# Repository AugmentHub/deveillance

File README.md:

# Deveillance Devices
We started this project as we have seen an increase in potentially privacy invading devices, such as wearable AI necklace, AR glasses that can take pictures of you, and more. Throughout the 2024 Augmentation Residency, we - Aida Baradari, Treyden Chiaravalloti, and Nasibe Nur Dundar - were thinking about ways of building what we coin "deveillance" technologies. 

**Deveillance** means off-watching, and we define deveillance technologies as technologies that give the power to the individual as to what data is collected and what is not collected. This can take the form of digital data and data potentially collected in the real world. This is, fundamentally, to build the use of these technologies for good and protective measures rather than for malicious intentions. 

There is still a lot of work to be done and we need more engineers tackling the problems of data collection in all realms. We started with Audio but this is a hub for everyone to contribute to a better design of deveillance devices. 

## Audio
Audio Jammers have existed for a while now but has been increasingly difficult to find affordable ones or even good, structured tutorials of how to make your own. This is how we built an audio jammer and how this works.

We are using a motor driver - more specifically the H-Bridge - L298N in order to generate a square wave signal. We formally tried using a signal generator with an amplifier but found it more difficult to get a non-noisy signal. 
The generated square-wave signal is based on the input voltage, for which you can use a power supply for now but we will eventually add batteries that are high enough (to get a good power output, we are currently using the H-Bridge that go up to 30V and 2A) but when we make it more wearable and you want to use it on your shelf, you may want to use a DC-DC Converter, upping the voltage of a generic LiPo battery. 

We are explaining how the Physics behind this works and then also how to make it yourself. 

### Wait, but why does it work? 
In a very simple way of explaining, without needing much physics background: Microphones have diaphragms. When sound hits that diaphragm, it vibrates it, and that movement creates electrical signals (in an abstract way of explaining it). 
Now, sound has different frequencies. We can hear a certain range of frequencies (20Hz to 20kHz) but below or higher than that humans can generally not hear. If you are close enough to our hearing frequency, however, the diaphragm of the microphone can sometimes pick it up. 
And because of this, your voice will be overridden. It cannot be filtered out. 

### Make It Yourself
- [Transducers](https://en.wikipedia.org/wiki/Transducer): For the bigger version, we are currently using the [2223-CUSA-T601-150-2400-TH-ND](https://www.digikey.com/en/products/detail/same-sky-formerly-cui-devices/CUSA-T601-150-2400-TH/16579211). 
- Arduino Nano (or any other Arduino / microcontroller device)

**Putting Things Together**
Here is how we are currently wiring things together (though the topology is very likely to change) :

### PCB Design 
Within this directory you will also find a PCB design with the L298N chip on board, battery charging circuit and more included. 
The data parts we are using are the following: 

- TP4056: 1A Standalone Linear Li-Ion Battery Charger with Thermal Regulation. This is for charging our battery and is connected to a USB port. You can find the datasheet [here](https://dlnmh9ip6v2uc.cloudfront.net/datasheets/Prototyping/TP4056.pdf). 
- DW01A: this is a battery protection IC. You can read more about it [here](https://hmsemi.com/downfile/dw01a.pdf)
- XL6009: this is our boost converter IC, which has a wide bandwidth. Find more information [here](https://www.haoyuelectronics.com/Attachment/XL6009/XL6009-DC-DC-Converter-Datasheet.pdf).
- L298N: this is our Hbridge to create our Ultrasonic wave.

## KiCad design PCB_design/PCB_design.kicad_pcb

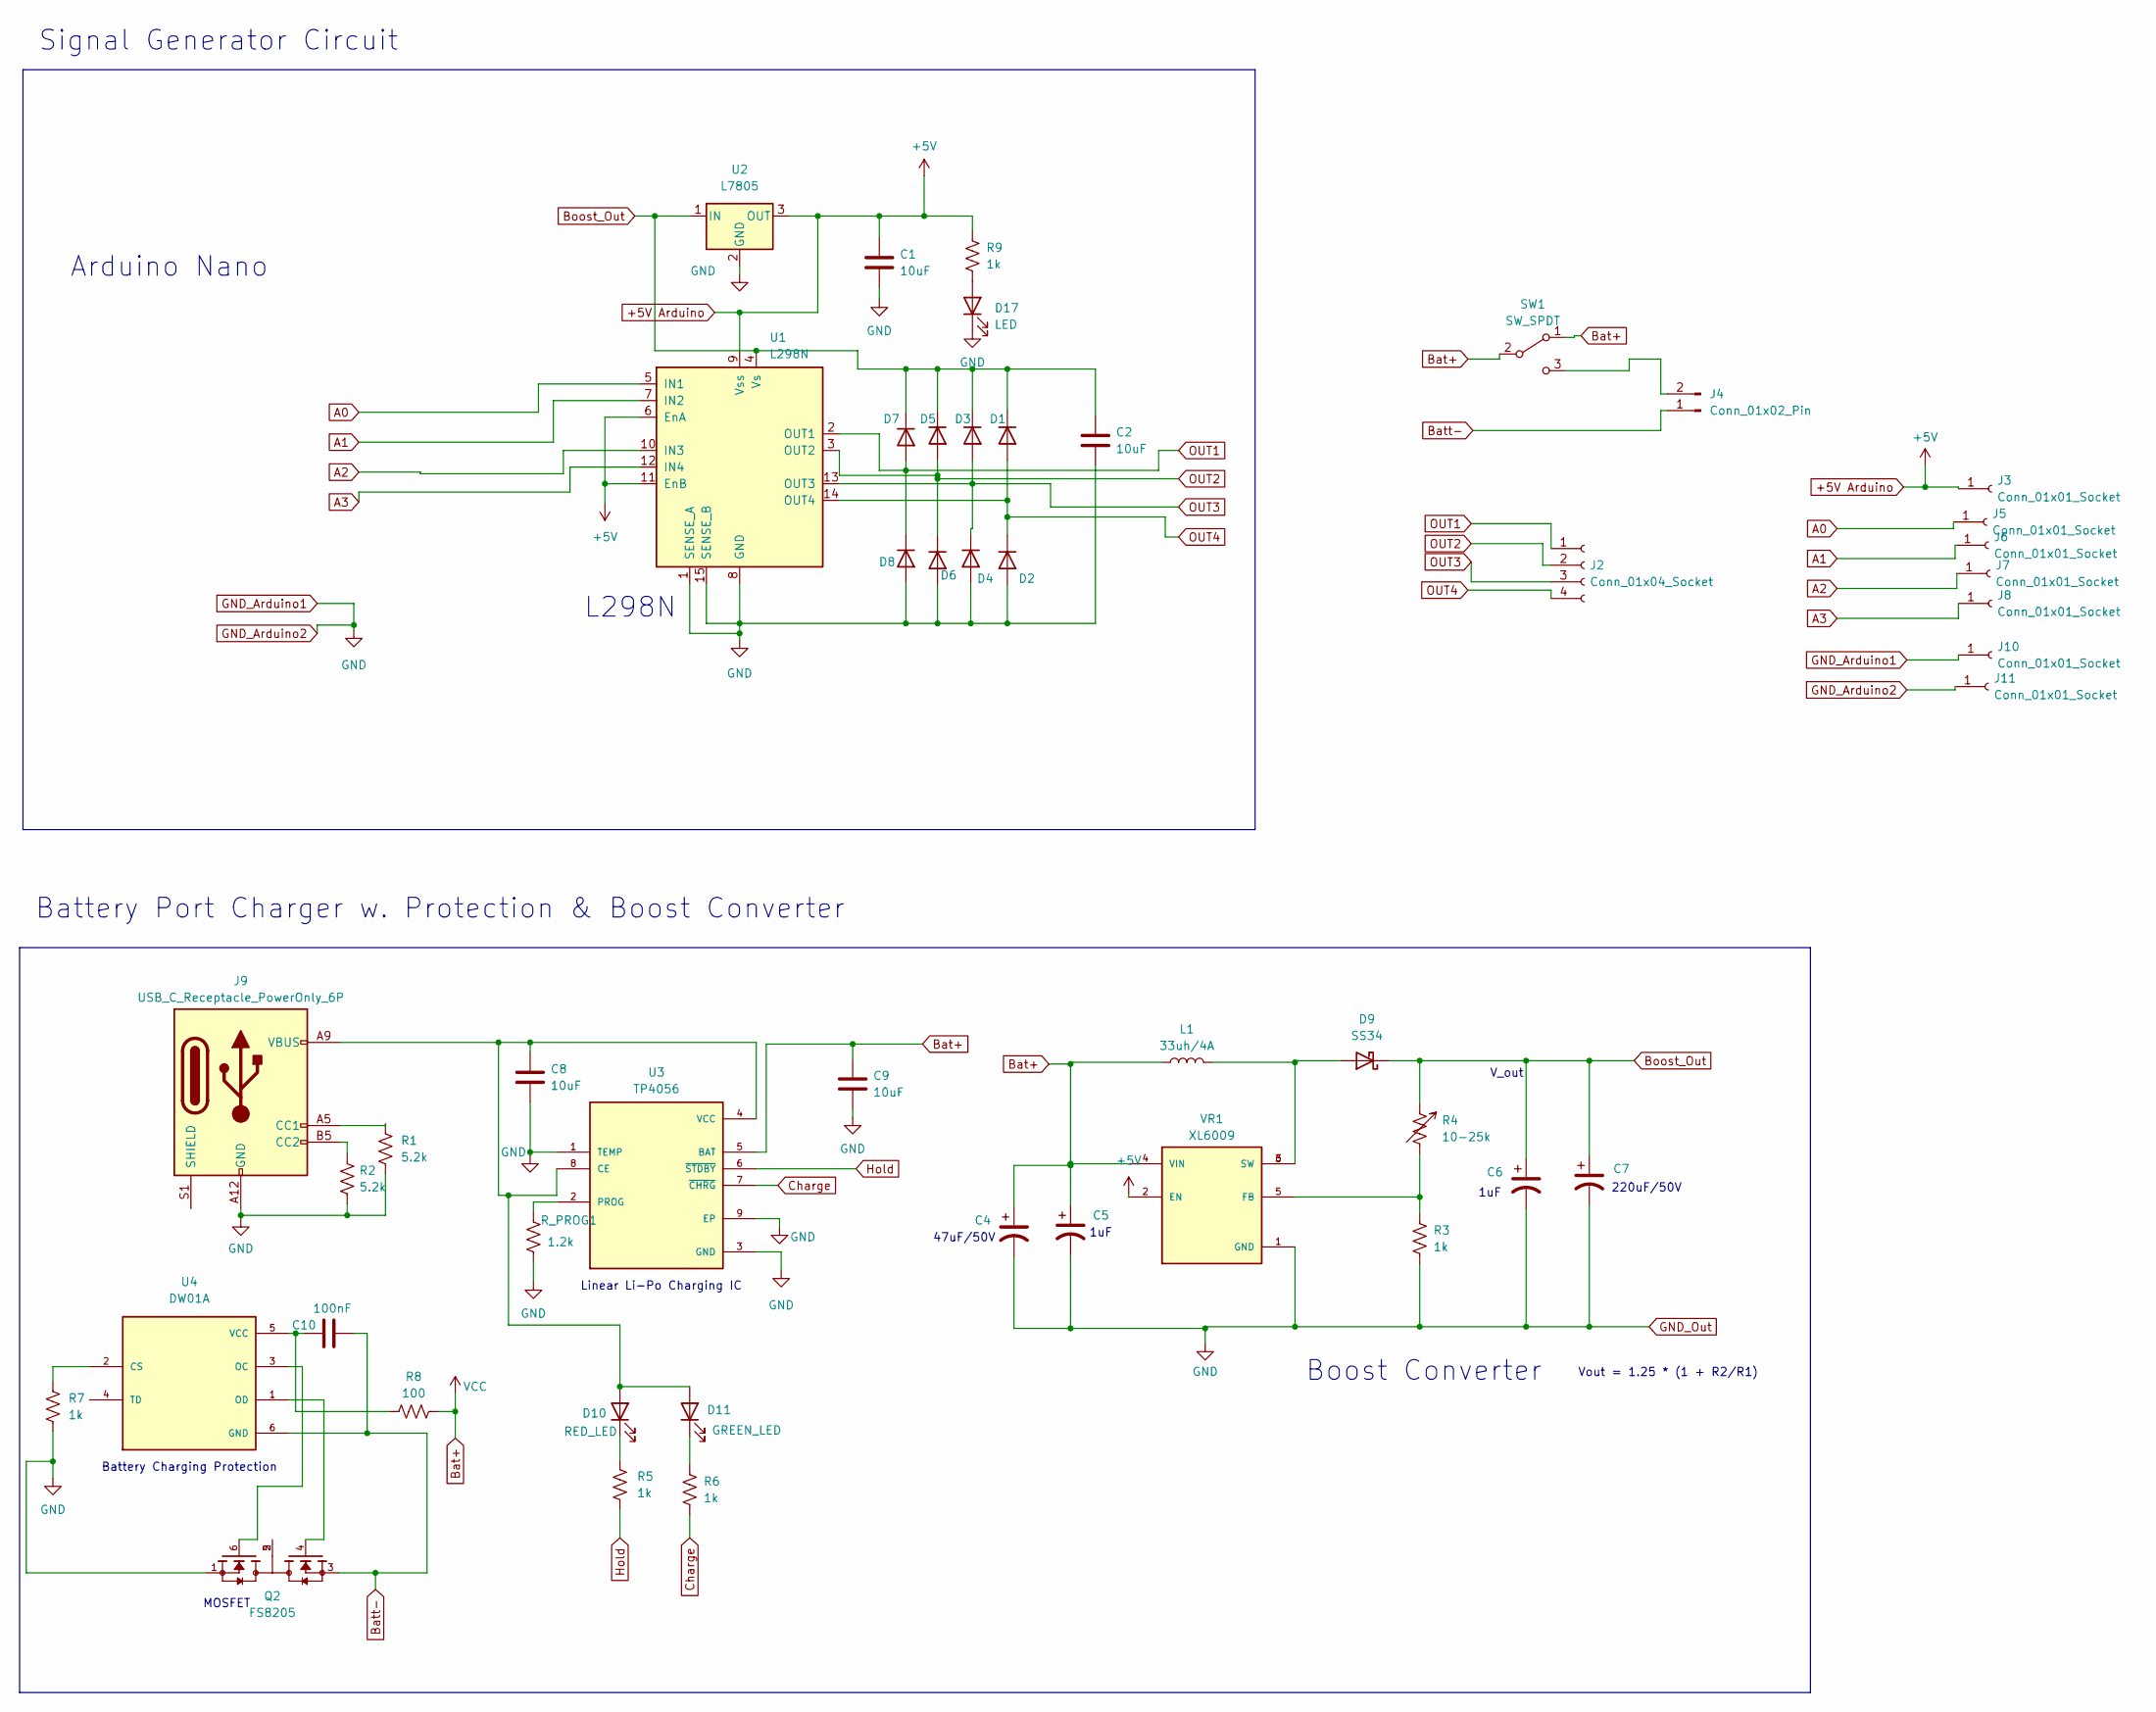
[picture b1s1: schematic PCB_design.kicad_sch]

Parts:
C1, C2, C8, C9: 10uF; C_0603_1608Metric_Pad1.08x0.95mm_HandSolder
C4: 47uF/50V; CP_Elec_6.3x7.7
C5, C6: 1uF; C_0603_1608Metric_Pad1.08x0.95mm_HandSolder
C7: 220uF/50V; CAP-SMD_BD10.0-L10.3-W10.3-FD
C10: 100nF; C_0603_1608Metric_Pad1.08x0.95mm_HandSolder
D1, D2, D3, D4, D5, D6, D7, D8: 1N5400; D_0805_2012Metric_Pad1.15x1.40mm_HandSolder
D9: SS34; DIOM8059X256N
D10: RED_LED; LED_0201_0603Metric_Pad0.64x0.40mm_HandSolder
D11: GREEN_LED; LED_0201_0603Metric_Pad0.64x0.40mm_HandSolder
D17: LED; LED_0201_0603Metric_Pad0.64x0.40mm_HandSolder
J2: Conn_01x04_Socket; PinHeader_1x04_P1.00mm_Vertical
J3, J5, J6, J7, J8, J10, J11: Conn_01x01_Socket; TestPoint_THTPad_1.0x1.0mm_Drill0.5mm
J4: Conn_01x02_Pin; JST_EH_S2B-EH_1x02_P2.50mm_Horizontal
J9: USB_C_Receptacle_PowerOnly_6P; USB_C_Receptacle_GCT_USB4135-GF-A_6P_TopMnt_Horizontal
L1: 33uh/4A; ND-SMD_L11.6-W10.1_final_13mm
Q2: FS8205; SOT95P280X145-6N; PARTREV 1.9
R1, R2: 5.2k; R_0603_1608Metric_Pad0.98x0.95mm_HandSolder
R3, R5, R6, R7, R9: 1k; R_0603_1608Metric_Pad0.98x0.95mm_HandSolder
R4: 10-25k; Potentiometer_Bourns_3224X_Vertical
R8: 100; R_0603_1608Metric_Pad0.98x0.95mm_HandSolder
R_PROG1: 1.2k; R_0603_1608Metric_Pad0.98x0.95mm_HandSolder
SW1: SW_SPDT; SW_MINI-SPDT-SW
U1: L298N; TO127P2020X500X2100-15
U2: L7805; VREG_L78M05CDT
U3: TP4056; SOP127P600X175-9N
U4: DW01A; SOT95P280X145-6N; PARTREV 1.8
VR1: XL6009; DPAK170P1435X465-6N; PARTREV 1.1

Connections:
+5V Arduino: C1.1, J3.1, R9.1, U1.6 (EnA), U1.9 (Vss), U1.11 (EnB), U2.3 (OUT), VR1.2 (EN)
A0: J5.1, U1.5 (IN1)
A1: J6.1, U1.7 (IN2)
A2: J7.1, U1.10 (IN3)
A3: J8.1, U1.12 (IN4)
Bat+: C4.1, C5.1, C9.1, L1.1, R8.2, SW1.1 (A), SW1.2 (B), U3.5 (BAT), VR1.4 (VIN)
Batt-: C10.2, J4.1, Q2.3, U4.6 (GND)
Boost_Out: C2.1, C6.1, C7.1, D1.1 (K), D3.1 (K), D5.1 (K), D7.1 (K), D9.1 (A), R4.1, U1.4 (Vs), U2.1 (IN)
Charge: R6.2, U3.7 (~CHRG)
GND_Arduino1: C1.2, C2.2, C4.2, C5.2, C6.2, C7.2, C8.2, C9.2, D2.2 (A), D4.2 (A), D6.2 (A), D8.2 (A), D17.1 (K), J9.A12 (GND), J9.B12 (GND), J10.1, J11.1, Q2.1, R1.2, R2.2, R3.2, R7.2, R_PROG1.2, U1.1 (SENSE_A), U1.8 (GND), U1.15 (SENSE_B), U2.2 (GND), U3.1 (TEMP), U3.3 (GND), U3.9 (EP), VR1.1 (GND)
Hold: R5.2, U3.6 (~STDBY)
unnamed: D9.2 (B), L1.2, VR1.3 (SW), VR1.6 (SW)
unnamed: C8.1, D10.2 (A), D11.2 (A), J9.A9 (VBUS), J9.B9 (VBUS), U3.4 (VCC), U3.8 (CE)
unnamed: D10.1 (K), R5.1
unnamed: D11.1 (K), R6.1
unnamed: D17.2 (A), R9.2
unnamed: J4.2, SW1.3 (C)
unnamed: J9.A5 (CC1), R1.1
unnamed: J9.B5 (CC2), R2.1
unnamed: Q2.2, Q2.5
unnamed: R_PROG1.1, U3.2 (PROG)
unnamed: R7.1, U4.2 (CS)
unnamed: Q2.6, U4.3 (OC)
unnamed: Q2.4, U4.1 (OD)
unnamed: C10.1, R8.1, U4.5 (VCC)
unnamed: R3.1, R4.2, VR1.5 (FB)
OUT1: D7.2 (A), D8.1 (K), J2.1, U1.2 (OUT1)
OUT2: D5.2 (A), D6.1 (K), J2.2, U1.3 (OUT2)
OUT3: D3.2 (A), D4.1 (K), J2.3, U1.13 (OUT3)
OUT4: D1.2 (A), D2.1 (K), J2.4, U1.14 (OUT4)

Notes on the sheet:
Battery Charging Protection
Signal Generator Circuit
1uF
L298N
Battery Port Charger w. Protection & Boost Converter
MOSFET
Vout = 1.25 * (1 + R2/R1)
47uF/50V
V_out
Boost Converter
Linear Li-Po Charging IC
220uF/50V
Arduino Nano

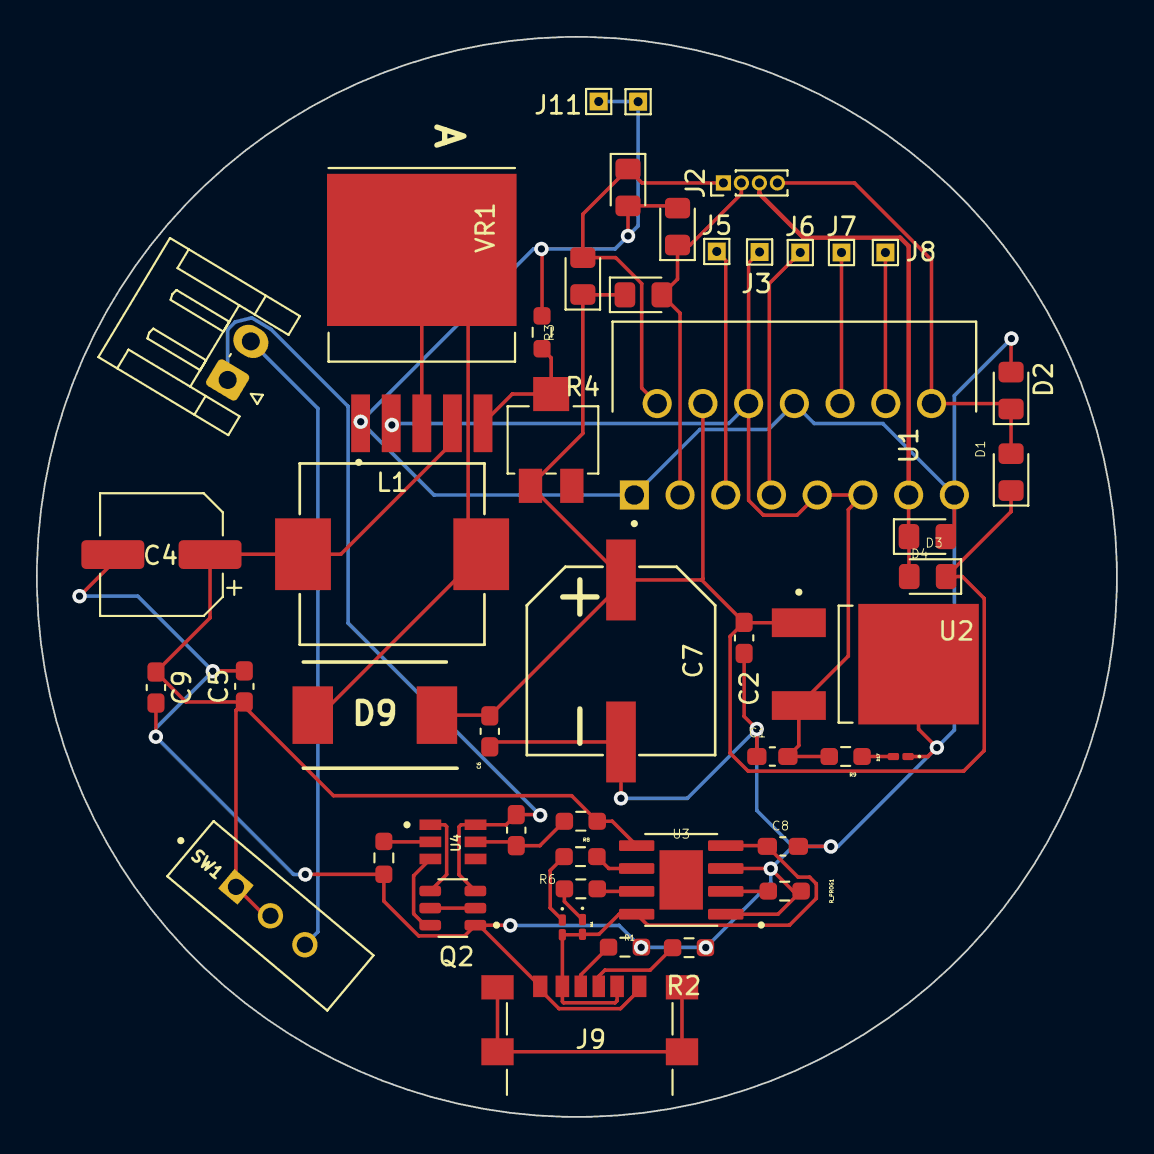
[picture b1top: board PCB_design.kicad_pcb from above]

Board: 2 copper layers, 60.0 x 60.0 mm, 49 parts (0 on the bottom side), 30 nets.

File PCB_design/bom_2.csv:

Comment;Designator;Footprint
1N5400;D5,D8,D7,D6,D4,D3,D2;D_0805_2012Metric_Pad1.15x1.40mm_HandSolder
1uF;C5;C_0201_0603Metric_Pad0.64x0.40mm_HandSolder
L7805;U2;VREG_L78M05CDT
Conn_01x01_Socket;J3,J10,J11,J6,J5,J7,J8;TestPoint_THTPad_1.0x1.0mm_Drill0.5mm
10uF;C9,C2,C8,C1;C_0603_1608Metric_Pad1.08x0.95mm_HandSolder
1k;R6,R3,R9,R7,R5;R_0603_1608Metric_Pad0.98x0.95mm_HandSolder
USB_C_Receptacle_PowerOnly_6P;J9;USB_C_Receptacle_GCT_USB4135-GF-A_6P_TopMnt_Horizontal
5.2k;R1,R2;R_0603_1608Metric_Pad0.98x0.95mm_HandSolder
L298N;U1;TO127P2020X500X2100-15
47uF/50V;C4;CAPAE1050X1050N
Conn_01x04_Socket;J2;PinHeader_1x04_P1.00mm_Vertical
RED_LED;D10;LED_0201_0603Metric_Pad0.64x0.40mm_HandSolder
XL6009;VR1;DPAK170P1435X465-6N
SS34;D9;DIOM8059X256N
100;R8;R_0603_1608Metric_Pad0.98x0.95mm_HandSolder
FS8205A;Q1;SOP65P640X120-8N
220uF/50V;C7;CAPAE1050X1050N
Conn_01x02_Pin;J4;JST_EH_S2B-EH_1x02_P2.50mm_Horizontal
33uh/4A;L1;L_7.3x7.3_H3.5
TP4056;U3;SOP127P600X175-9N
1.2k;R_PROG1;R_0603_1608Metric_Pad0.98x0.95mm_HandSolder
10-25k;R4;Potentiometer_Bourns_3224X_Vertical
GREEN_LED;D11;LED_0201_0603Metric_Pad0.64x0.40mm_HandSolder
DW01A;U4;SOT95P280X145-6N
LED;D17;LED_0201_0603Metric_Pad0.64x0.40mm_HandSolder
100nF;C10;C_0603_1608Metric_Pad1.08x0.95mm_HandSolder
1uF;C6;C_0603_1608Metric_Pad1.08x0.95mm_HandSolder
1N5400;D1;D_0805_2012Metric_Pad1.15x1.40mm_HandSolder

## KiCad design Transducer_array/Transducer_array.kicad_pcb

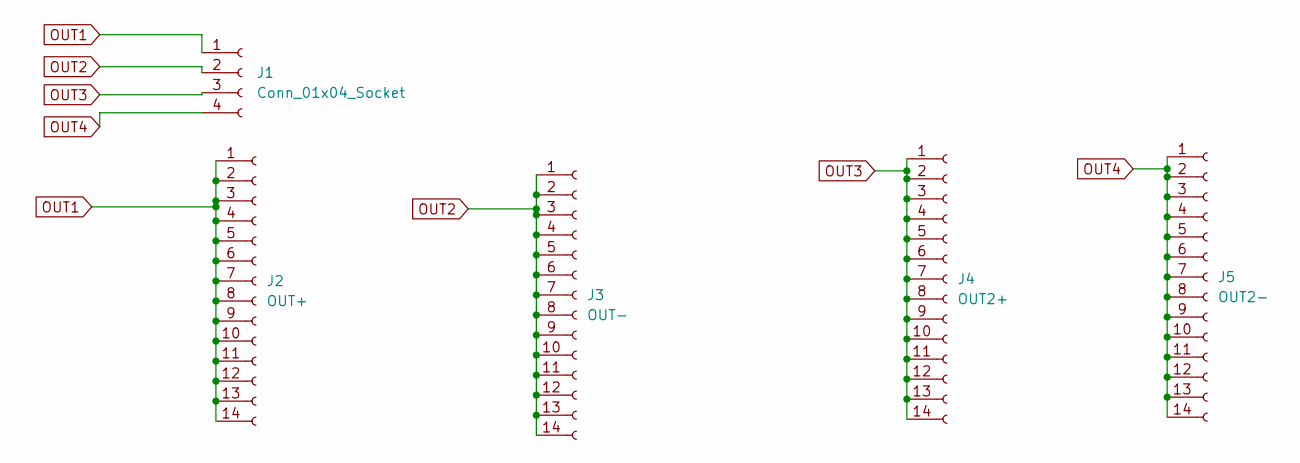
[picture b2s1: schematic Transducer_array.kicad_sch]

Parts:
J1: Conn_01x04_Socket; PinSocket_1x04_P1.00mm_Vertical
J2: OUT+; PinSocket_1x14_P1.00mm_Vertical
J3: OUT-; PinSocket_1x14_P1.00mm_Vertical
J4: OUT2+; PinSocket_1x14_P1.00mm_Vertical
J5: OUT2-; PinSocket_1x14_P1.00mm_Vertical

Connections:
OUT1: J1.1, J2.1, J2.2, J2.3, J2.4, J2.5, J2.6, J2.7, J2.8, J2.9, J2.10, J2.11, J2.12, J2.13, J2.14
OUT2: J1.2, J3.1, J3.2, J3.3, J3.4, J3.5, J3.6, J3.7, J3.8, J3.9, J3.10, J3.11, J3.12, J3.13, J3.14
OUT3: J1.3, J4.1, J4.2, J4.3, J4.4, J4.5, J4.6, J4.7, J4.8, J4.9, J4.10, J4.11, J4.12, J4.13, J4.14
OUT4: J1.4, J5.1, J5.2, J5.3, J5.4, J5.5, J5.6, J5.7, J5.8, J5.9, J5.10, J5.11, J5.12, J5.13, J5.14

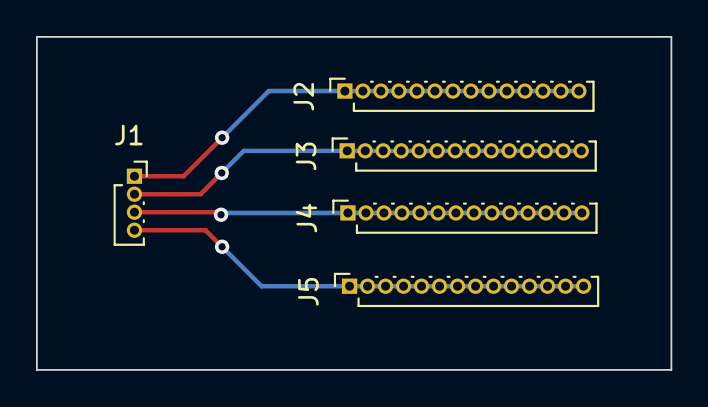
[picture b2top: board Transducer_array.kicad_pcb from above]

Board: 2 copper layers, 35.2 x 18.5 mm, 5 parts (0 on the bottom side), 4 nets.

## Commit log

2024-07-22 Coded simple sine wave output from an Arduino device for testing purposes
2024-07-23 Fixed error in sending waveform + added comments explaining code. Functional Code for sending 25kHz wave through Motor Driver to Transducers
2024-07-25 Added code to send signals through AD9833 Signal Generator
2024-07-26 Modified code to switch between waveforms.
2024-08-07 Added Signal Generation
2024-08-08 Added L298N square wave generation of 25kHz as a test
2024-08-10 Fixed code for square waves + sweep
2024-10-02 Updates that were never pushed
2024-10-03 Old updates that were not pushed
2024-10-03 Fixed folder structure
2024-10-03 Added schematic
2024-11-01 Added PCB Design file
2024-11-02 Updated PCB Design
2024-11-06 Added ICs for battery charging and battery charging protection to implement with Boost Converter on PCB.
2024-11-07 Finished v0 of schematic
2024-11-09 Added most of the footprints and imported into PCB designer
2024-11-11 Progress on PCB, added different capacitors, continued routing
2024-11-12 Finished routing of PCB, v0
2024-11-12 Fixed routing to bottom layer
2024-11-12 Removed GND to Bat- connection and rereouted
2024-11-12 Fixed issues surrounding wiring, Vss to Vs for 12V, CE actually enabled
2024-11-14 Fix errors on circuit schematic and reorder PCB layout
2024-11-17 Finished PCB design and outline, added interactive html design
2024-11-17 Added PCB design pdf
2024-11-17 Updated circuit schematic
2024-11-17 Actually added the new schematic
2024-11-17 Organized folder structure running
2024-11-17 Moved HTML Web visualization to another repo to link to
2024-11-17 Added design for in parallel transducer plug in
2024-11-25 Add new PCB Design
